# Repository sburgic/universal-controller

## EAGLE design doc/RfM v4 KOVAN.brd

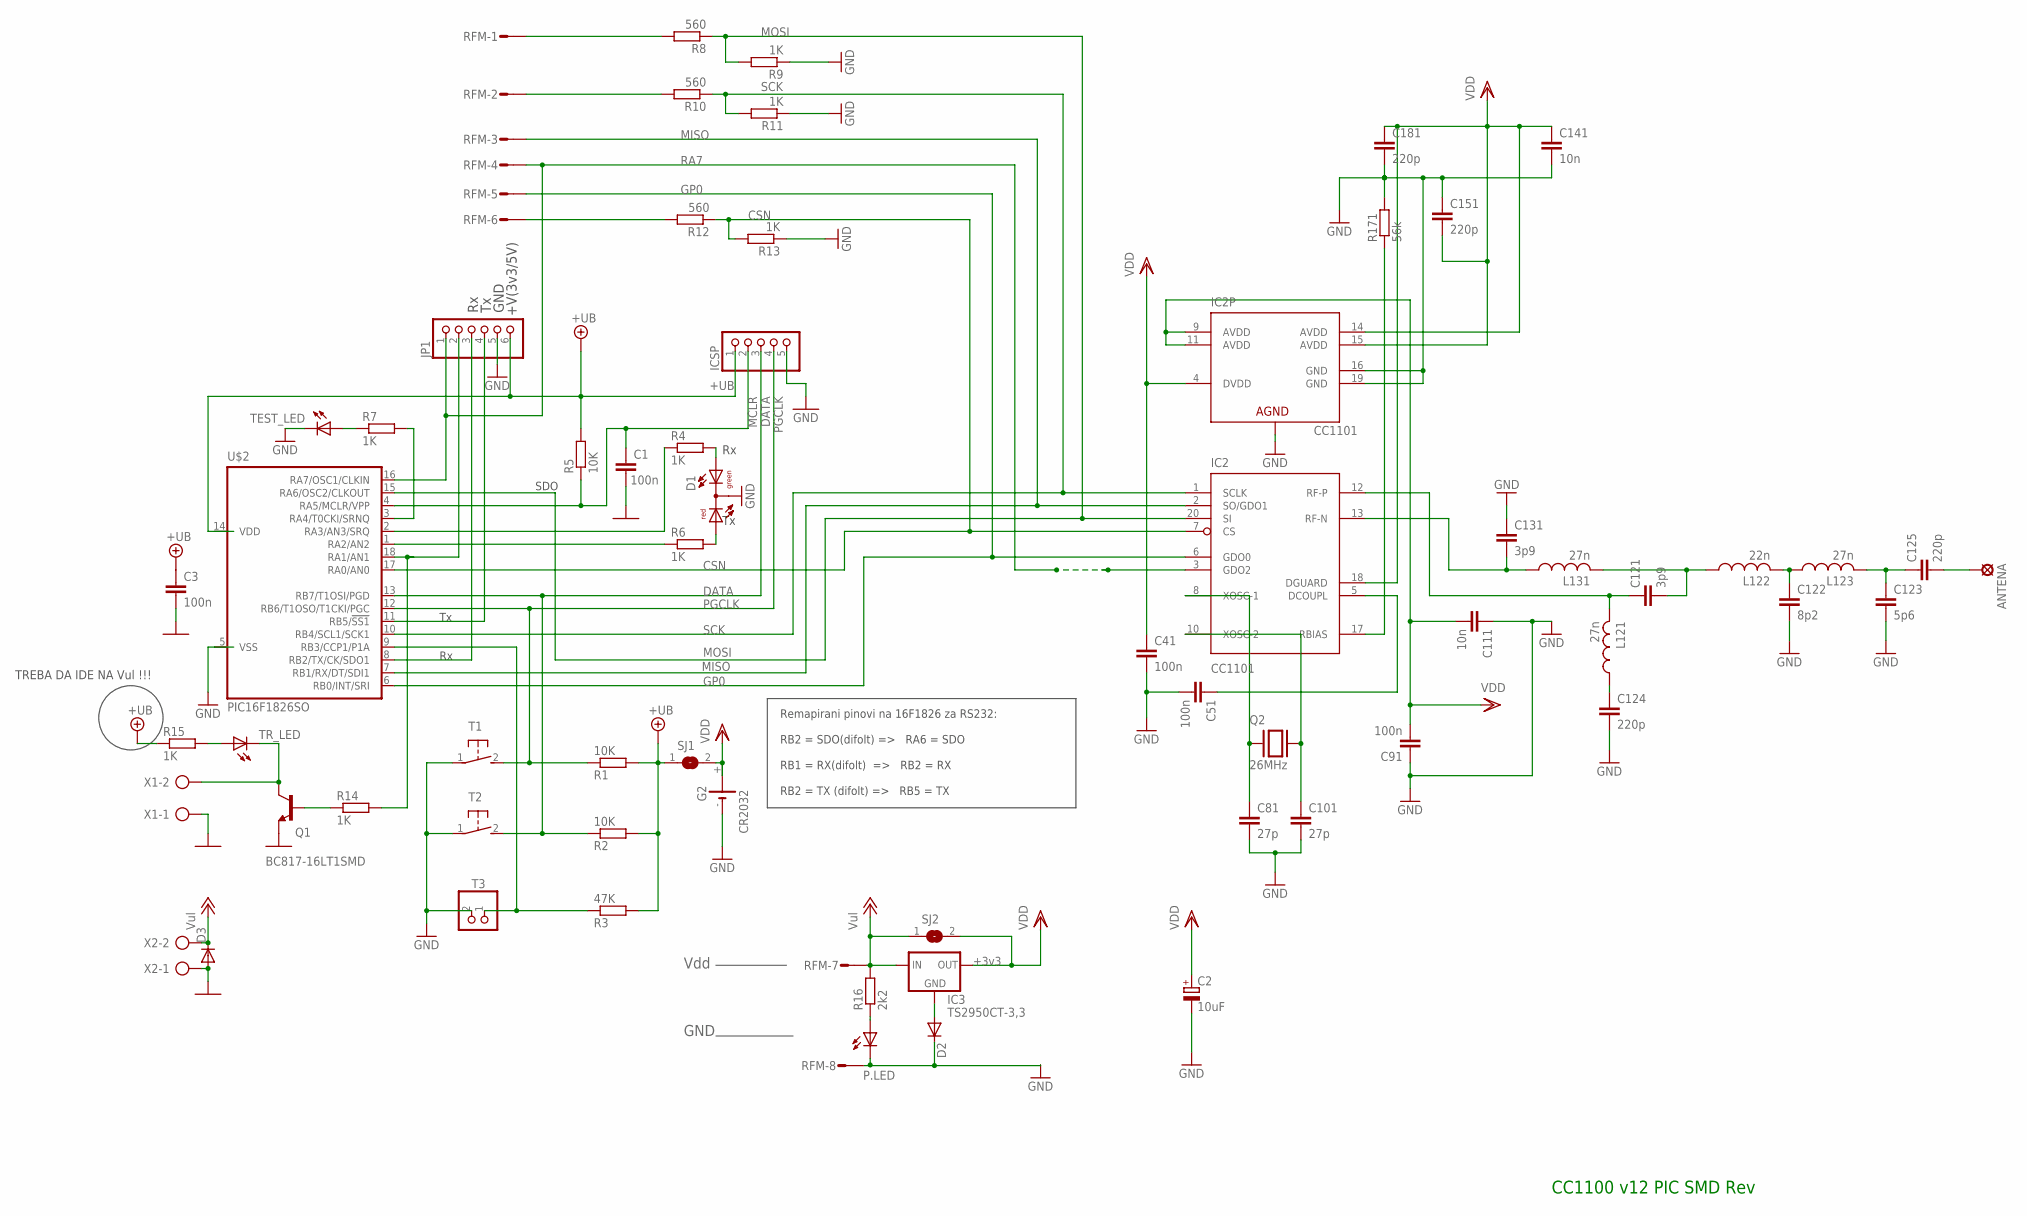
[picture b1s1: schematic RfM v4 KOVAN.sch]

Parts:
ANTENA: SE13
C1: 100n; C0805
C2: 10uF; ALUCON
C3: 100n; C1206
C41, C51, C91: 100n; C0402
C81, C101: 27p; C0402
C111, C141: 10n; C0402
C121, C131: 3p9; C0402
C122: 8p2; C0402
C123: 5p6; C0402
C124, C125, C151, C181: 220p; C0402
D1: DUOLED2X5.; DUOLED2X5*
D2, D3: 1N4004SMD; 1N4007-SMD
G2: CR2032; CR2032--
IC2: CC1101; QLP-20
IC3: TS2950CT-3,3; 78LXX
ICSP: PINHD-1X5.; 1X05.
JP1: PINHD-1X6.; 1X06.
L121, L123, L131: 27n; C0402
L122: 22n; C0402
P.LED: zelena; CHIPLED_0805
Q1: BC817-16LT1SMD; SOT23-BEC
Q2: 26MHz; SMD
R1, R2: 10K; R0805
R3: 47K; R0603
R4, R6: 1K; R0805
R5: 10K; R0603
R7, R9, R11, R13, R15: 1K; R0603
R8, R10, R12: 560; R0603
R14: 1K; R1206
R16: 2k2; R0805
R171: 56k; R0402
RFM: MICROMATCH-8'; MICROMATCH-8..
SJ1, SJ2: SJ
T1, T2: 10-XX-1'; 3BF-10XX-1.
T3: PINHD-1X2.; 1X02.
TEST_LED: TEST_LED; CHIPLED_0805
TR_LED: TEST_LED; CHIPLED_0805
U$2: PIC16F1826SO; SO-18W
X1, X2: AK300/2

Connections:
+12V: D3.C, IC3.IN, R16.2, RFM.7, SJ2.1, X2.2
+UB: C3.2, ICSP.1, JP1.6, R1.2, R2.2, R3.2, R5.2, R15.1, SJ1.1, U$2.14 (VDD)
CSN: IC2.7 (CS), R12.1, R13.2, U$2.17 (RA0/AN0)
DATA: ICSP.3, R2.1, T2.2 (S), U$2.13 (RB7/T1OSI/PGD)
DCOUPL: C51.2, IC2.5 (DCOUPL)
GND: C1.1, C2.P$1 (-), C3.1, C41.1, C51.1, C81.1, C91.2, C101.1, C111.2, C122.1, C123.1, C124.1, C131.2, C141.1, C151.2, C181.1, D1.K (C), D2.C, D3.A, G2.-, IC2.16 (GND), IC2.19 (GND), IC2.21 (AGND), ICSP.5, JP1.5, Q1.E, R9.1, R11.1, R13.1, R171.2, RFM.8, T1.1, T2.1, T3.2, TEST_LED.C, U$2.5 (VSS), X1.1, X2.1
GP0: IC2.6 (GDO0), RFM.5, U$2.6 (RB0/INT/SRI)
MCLR: C1.2, ICSP.2, R5.1, U$2.4 (RA5/MCLR/VPP)
MISO: IC2.2 (SO/GDO1), RFM.3, U$2.7 (RB1/RX/DT/SDI1)
MOSI: IC2.20 (SI), R8.1, R9.2, U$2.15 (RA6/OSC2/CLKOUT)
unnamed: IC2.17 (RBIAS), R171.1
unnamed: C101.2, IC2.10 (XOSC-2), Q2.P$5 (2)
unnamed: C81.2, IC2.8 (XOSC-1), Q2.P$3 (1)
unnamed: C131.1, IC2.13 (RF-N), L131.2
unnamed: C121.2, IC2.12 (RF-P), L121.1
unnamed: C124.2, L121.2
unnamed: C123.2, C125.2, L123.1
unnamed: C122.2, L122.1, L123.2
unnamed: ANTENA.MP, C125.1
unnamed: D1.AG, R4.2
unnamed: R7.1, TEST_LED.A
unnamed: C121.1, L122.2, L131.1
unnamed: D1.AR, R6.2
unnamed: JP1.2, R14.2, U$2.18 (RA1/AN1)
unnamed: Q1.B, R14.1
unnamed: R15.2, TR_LED.A
unnamed: Q1.C, TR_LED.C, X1.2
unnamed: D2.A, IC3.GND
unnamed: R8.2, RFM.1
unnamed: R10.2, RFM.2
unnamed: R12.2, RFM.6
unnamed: P.LED.A, R16.1
PGCLK: ICSP.4, R1.1, T1.2 (S), U$2.12 (RB6/T1OSO/T1CKI/PGC)
RA2: R6.1, U$2.1 (RA2/AN2)
RA3: R4.1, U$2.2 (RA3/AN3/SRQ)
RA4: R7.2, U$2.3 (RA4/T0CKI/SRNQ)
RA7: JP1.1, RFM.4, U$2.16 (RA7/OSC1/CLKIN)
RB3: R3.1, T3.1, U$2.9 (RB3/CCP1/P1A)
RX: JP1.3, U$2.8 (RB2/TX/CK/SDO1)
SCK: IC2.1 (SCLK), R10.1, R11.2, U$2.10 (RB4/SCL1/SCK1)
TX: JP1.4, U$2.11 (RB5/!SS1)
VDD: C2.P$4 (+), C41.2, C91.1, C111.1, C141.2, C151.1, C181.2, G2.+, G2.+@1 (+), IC2.4 (DVDD), IC2.9 (AVDD), IC2.11 (AVDD), IC2.14 (AVDD), IC2.15 (AVDD), IC2.18 (DGUARD), IC3.OUT, SJ1.2, SJ2.2

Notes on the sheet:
CC1100 v12 PIC SMD Rev
Vdd
GND
+3v3
Remapirani pinovi na 16F1826 za RS232:
RB2 = SDO(difolt) => RA6 = SDO
RB1 = RX(difolt) => RB2 = RX
RB2 = TX (difolt) => RB5 = TX
+V(3v3/5V)
SDO
TREBA DA IDE NA Vul !!!

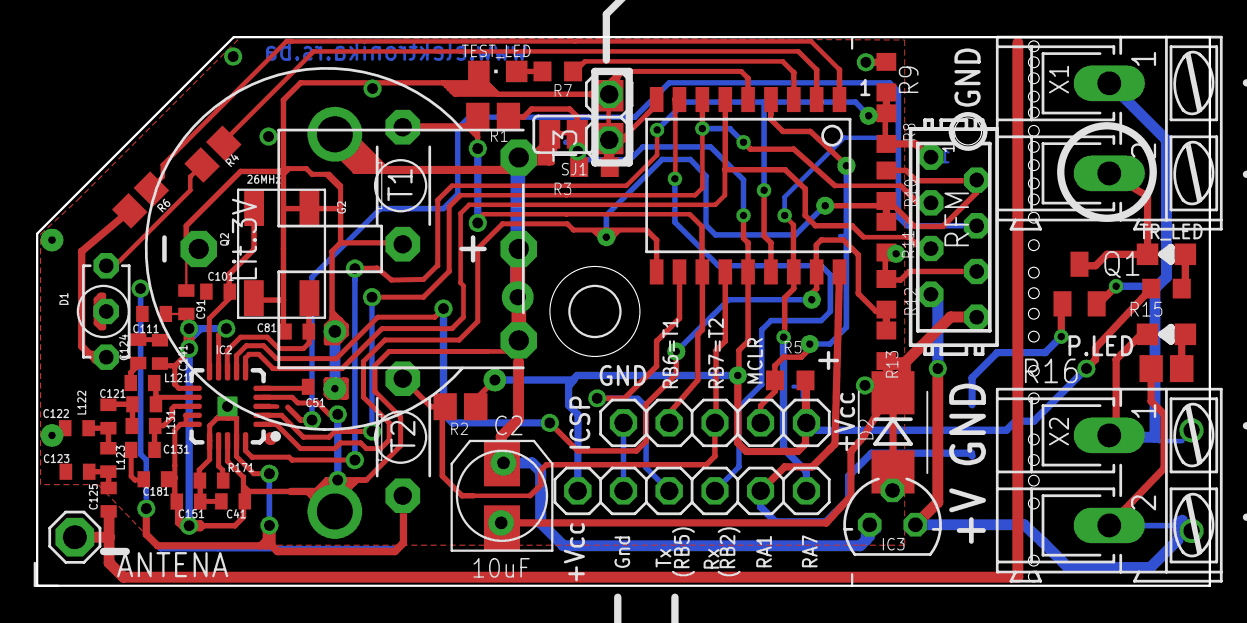
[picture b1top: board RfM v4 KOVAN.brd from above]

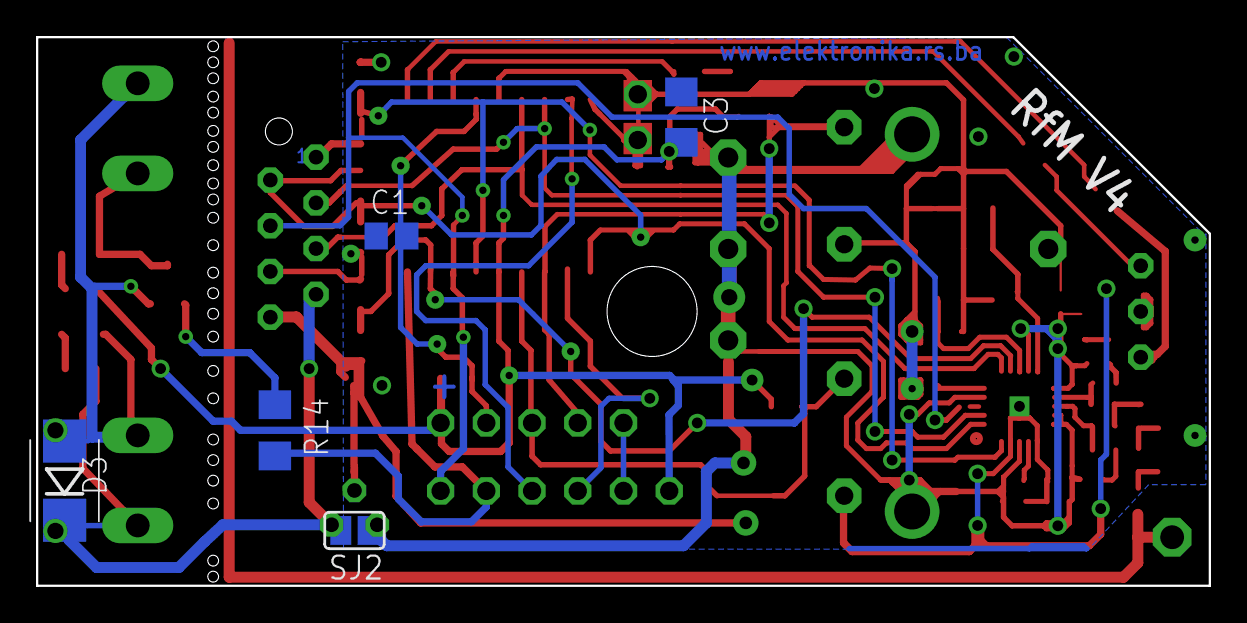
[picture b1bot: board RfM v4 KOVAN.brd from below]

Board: 3 copper layers, 65.2 x 30.5 mm, 63 parts (5 on the bottom side), 42 nets.

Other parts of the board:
U$1: KUTIJA_ZA_DALJINSKI

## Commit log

2020-12-19 add .gitignore
2020-12-19 add PCBs
2020-12-19 add initial source code
2021-01-06 finalize bluetooth communication
2021-01-16 fix bluetooth timeout values
2021-01-22 add cc1101; remove gsm support
2021-01-24 add suport for iar compiler
2021-02-25 Add ver.1.0.0 (bluetooth only)
2021-02-25 Add GSM support
2021-02-25 Remove unused files
2021-02-26 Fix temperature output strings
2021-03-09 Add temperature hysteresis
2021-04-18 Add main board PCB ver.1.1
2021-04-18 Add RF board PCB ver.2.0
2021-04-21 Add doc folder
2021-07-24 Fix bug in Bluetooth initialization
